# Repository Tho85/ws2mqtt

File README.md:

# Reason for fork
After an evening of confusion why Visual Studio Code with PlatformIO was giving me constant errors compiling, as a lost resort I changed the name of the included "wifi.h" and the references to it, as it might in some way be conflichting with the <wifi.h> library. Miraculously it did suddenly compile without a hitch. I'm by no means a developer and this is my first Github fork, but I figured I'd share it if others run into the same problem.

# ws2mqtt - WiSafe2 to MQTT gateway

ws2mqtt is an inofficial gateway to connect WiSafe2 smoke, heat and CO detectors to your smart home.

The gateway consists of an ESP32 module that handles Wifi and MQTT communication and integrates with Home Assistant through MQTT auto discovery. It is connected to an Arduino that acts as an SPI/UART converter. The Arduino talks to an official WiSafe2 module that is connected to your smoke detector network.

## Disclaimer

This project is not related to or endorsed by the manufacturer of WiSafe2 devices. It is an unofficial hobby project.

:warning: **DO NOT USE THIS PROJECT FOR SAFETY-CRITICAL PURPOSES!** :warning:

This is a hobby project after all, so do not rely on it for your personal safety or the saftey of others. Always assume that it will not work in a case of emergency, and plan your emergency procedures accordingly. As the [license](LICENSE.md) states in more detail, I won't be liable for any damages incurred by this project.

## Pictures

## Supported devices

Tested:

- ST-630-DE(P) Smoke detector
- HT-630-EUT Heat detector

Not tested, but should be working:

- WST-630 Smoke alarm
- W2-CO-10X CO alarm
- FP1720W2-R Smoke alarm
- FP2620W2-R Smoke alarm

## Features

- [x] Smoke / heat detector states:
  - [x] Smoke / heat detected
  - [x] Battery state
  - [x] Radio module battery state
  - [x] Device attached to base
- [x] Test button detection
- [x] Combined test button / detection event (see Tips & troubleshooting)
- [x] Test all devices from Home Assistant

TODO:

- [ ] Test single device from Home Assistant
- [ ] Logging via MQTT
- [ ] ESP32 over-the-air updates

## Additional Hardware required

- [ESP32-DevKitC V4](https://docs.espressif.com/projects/esp-idf/en/latest/esp32/hw-reference/esp32/get-started-devkitc.html)
- [Arduino Pro Mini](https://www.arduino.cc/en/pmwiki.php?n=Main/ArduinoBoardProMini), or chinese clone
- [WiSafe2 module](https://www.directtradesupplies.co.uk/product.php/199997/fireangel-wisafe2-module--wireless-alarm-pairing--all-wisafe2--mains---battery-only--alarms-can-be-paired---white-)
- A 868 MHz antenna, e.g. stripped from a defective detector. Alternatively, an 8.8 cm long wire
- Custom PCB (see `PCB` folder). Alternatively, lots of breadboard wires (see [schematic](PCB/schematic.pdf))

## Setup

- Setup Arduino
  - Mount Arduino to PCB
  - Flash Arduino firmware (see `Firmware-Atmega` folder) via programmer
- Setup ESP32
  - Mount ESP32 to PCB
  - Configure your secrets in `Firmware-ESP/include/credentials.h` (see example)
  - Flash ESP32 firmware (see `Firmware-ESP` folder) via USB
- Power board via ESP32 USB connector
- Setup WiSafe2 module
  - Mount WiSafe2 module to PCB
  - Join WiSafe2 network
    - Push button on module for 5 seconds
    - Module LED should light up
    - Within 5 seconds, push test button on a different detector
    - Module LED should blink multiple times as a confirmation
- Mount ESP32, Arduino and WiSafe2 module on PCB
- Configure Home Assistant
  - The gateway and all detectors should be visible in the "Devices" tab
  - Create an automation that listens for the `alarm` event emitted by the gateway, see below

## Tips & troubleshooting

* The recommended way to react to smoke detection and test events in Home Assistant is to listen to the `alarm` event emitted by the `ws2mqtt Bridge` device. This event is fired when any of the connected detectors detects smoke, or when any of the detectors' test buttons is pressed. This way you can test your emergency scenes and automations by pressing a detector's test button.

* _The "smoke detected" sensor shows an unknown state_

  This is actually a deficiency of the WiSafe2 protocol. As far as I know, there is no way to query a device for the current smoke / heat detector state. Additionally, a "smoke detected" message is only sent once to other detectors, and not repeated later. So if you start the gateway while a "smoke detected" event is ongoing, there is no way for the gateway to know about that event. I decided to err on the side of caution and show the state of devices as "unknown".

* _The "battery" sensor, "docked" sensor etc. show an unknown state_

  To conserve battery power, the gateway does not actively query the state of these diagnostic sensors. The sensor state is only updated on change. The easiest way to force an update is to remove a detector from its base, wait a bit, and re-mount the device. This should update not only the "docked" sensor, but also the battery ones.

* What is the programming language you used, and why is it not perfect C?

  C is not my mother tongue, so it's nearly certain that there are race conditions, buffer overflows or bad C programming practices in the code. Feel free to file an issue to point things out, or even better file a pull request.

## License

See [LICENSE](LICENSE.md).

## Final notes

Shout out to **C19HOP** and his [WiSafe2-to-HomeAssistant-Bridge](https://github.com/C19HOP/WiSafe2-to-HomeAssistant-Bridge), for helping in reversing the protocol, and for giving me the motivation to finish this project I've been working on for the last months.

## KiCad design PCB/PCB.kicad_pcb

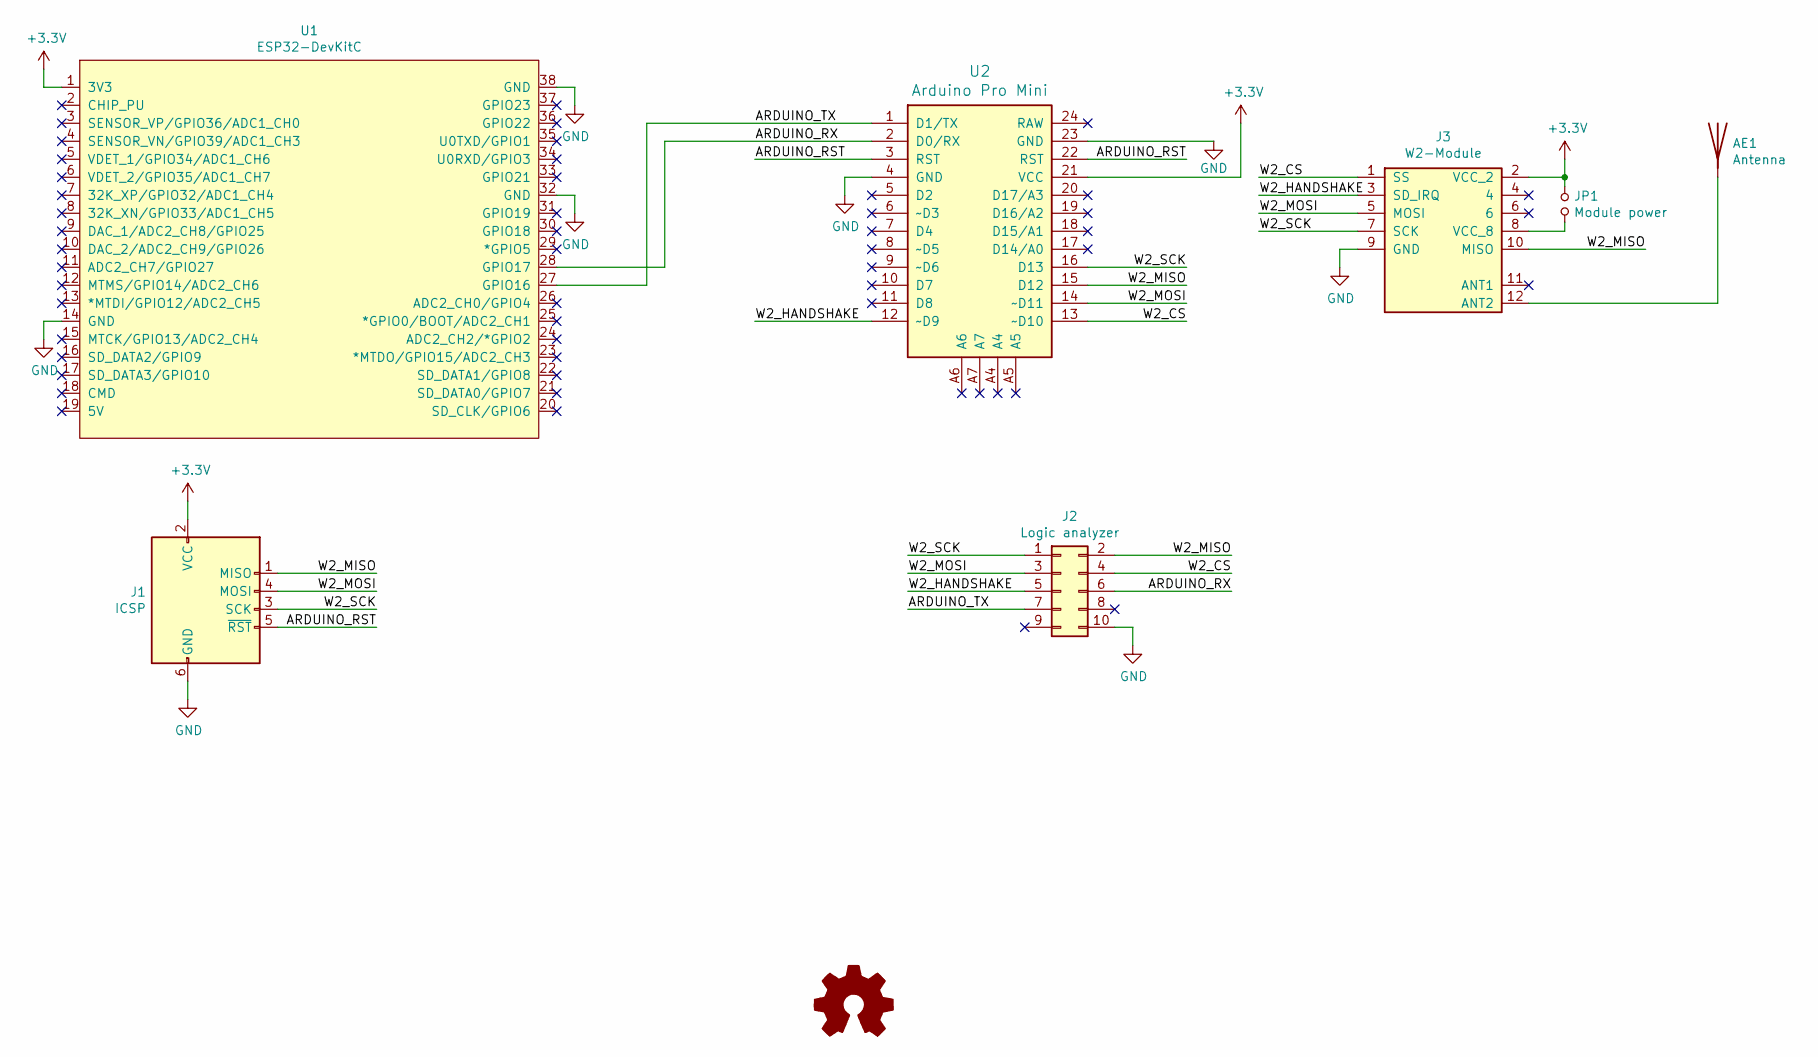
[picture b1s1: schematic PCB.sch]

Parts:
AE1: Antenna; PinHeader_1x01_P2.54mm_Vertical
J1: ICSP; IDC-Header_2x03_P2.54mm_Vertical
J2: Logic analyzer; IDC-Header_2x05_P2.54mm_Vertical
J3: W2-Module; W2-MM
JP1: Module power; SolderJumper-2_P1.3mm_Open_RoundedPad1.0x1.5mm
LOGO1: Logo_Open_Hardware_Small; OSHW-Logo_5.7x6mm_SilkScreen
U1: ESP32-DevKitC
U2: Arduino Pro Mini; Arduino_Pro_Mini

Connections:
+3V3: J1.2 (VCC), J3.2 (VCC_2), JP1.1, U1.1 (3V3), U2.21 (VCC)
/ARDUINO_RST: J1.5 (~RST), U2.3 (RST), U2.22 (RST)
/ARDUINO_RX: J2.6, U1.28 (GPIO17), U2.2 (D0/RX)
/ARDUINO_TX: J2.7, U1.27 (GPIO16), U2.1 (D1/TX)
/W2_CS: J2.4, J3.1 (SS), U2.13 (~~D10)
/W2_HANDSHAKE: J2.5, J3.3 (SD_IRQ), U2.12 (~~D9)
/W2_MISO: J1.1 (MISO), J2.2, J3.10 (MISO), U2.15 (D12)
/W2_MOSI: J1.4 (MOSI), J2.3, J3.5 (MOSI), U2.14 (~~D11)
/W2_SCK: J1.3 (SCK), J2.1, J3.7 (SCK), U2.16 (D13)
GND: J1.6 (GND), J2.10, J3.9 (GND), U1.14 (GND), U1.32 (GND), U1.38 (GND), U2.4 (GND), U2.23 (GND)
unnamed: AE1.1, J3.12 (ANT2)
unnamed: J3.8 (VCC_8), JP1.2

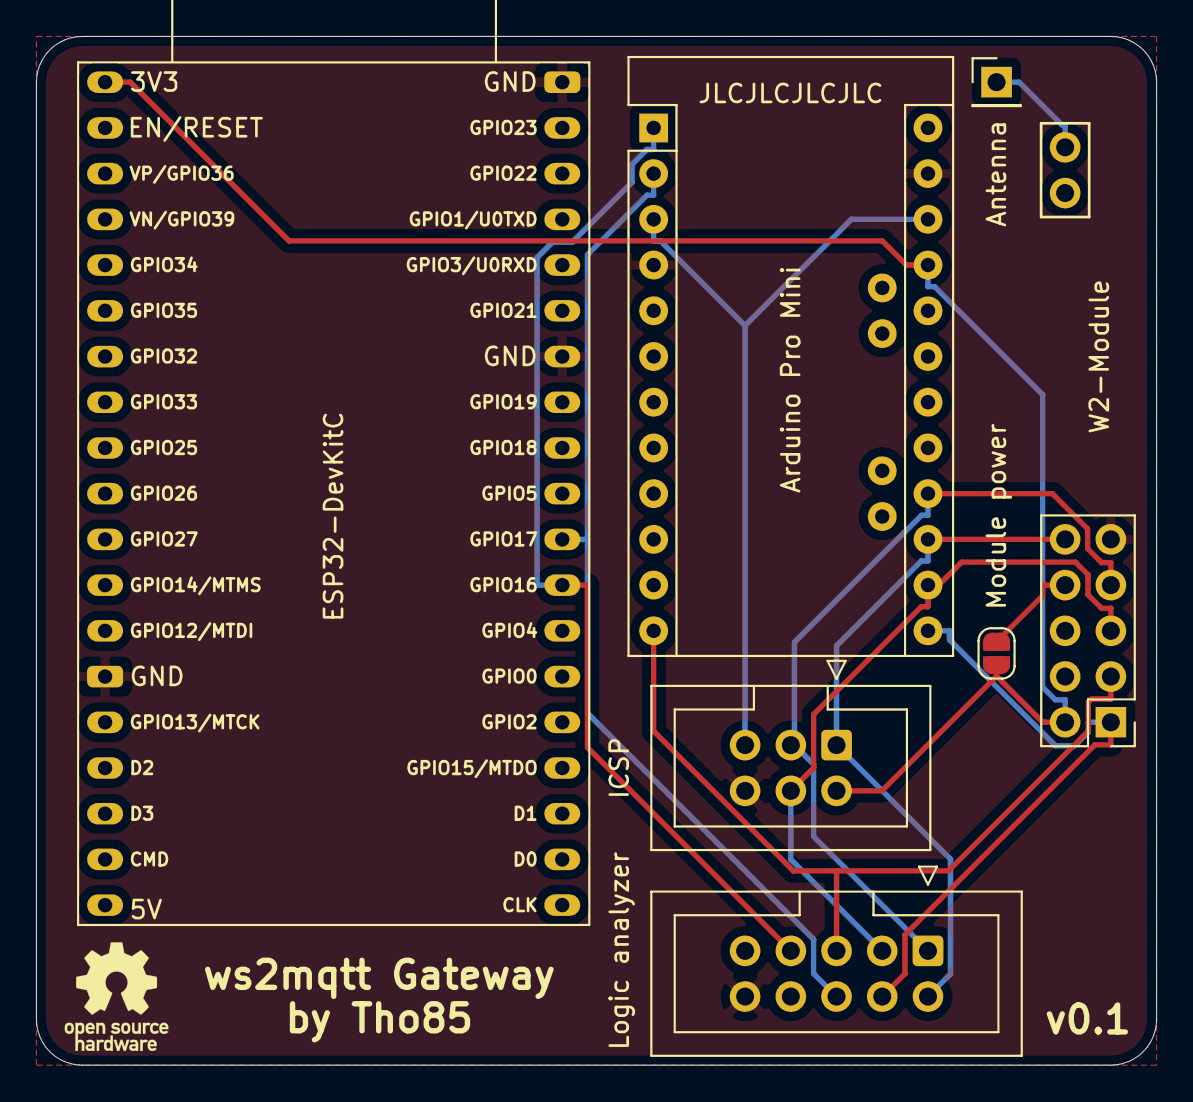
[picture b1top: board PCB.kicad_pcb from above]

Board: 2 copper layers, 62.2 x 57.2 mm, 8 parts (0 on the bottom side), 12 nets.

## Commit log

2022-03-12 Add README
2022-03-12 Rename LICENSE.md
2022-03-12 Add PCB schematic
2022-03-12 Add antenna info to readme
2022-03-12 Clarify readme
2022-03-12 Add shout out
2023-06-18 Rename wifi.h to wifi_inc.h
2023-08-12 Rename "wifi.h" to avoid issues with Arduino framework (#3)
    * Update wisafe2_rx.cpp
    * Update wifi.cpp
    * Update main.cpp
    * Update homeassistant.cpp
    * Rename wifi.h to wifi_inc.h
    * Update README.md
